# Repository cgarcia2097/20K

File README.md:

# numpad
Repository for the numpad project

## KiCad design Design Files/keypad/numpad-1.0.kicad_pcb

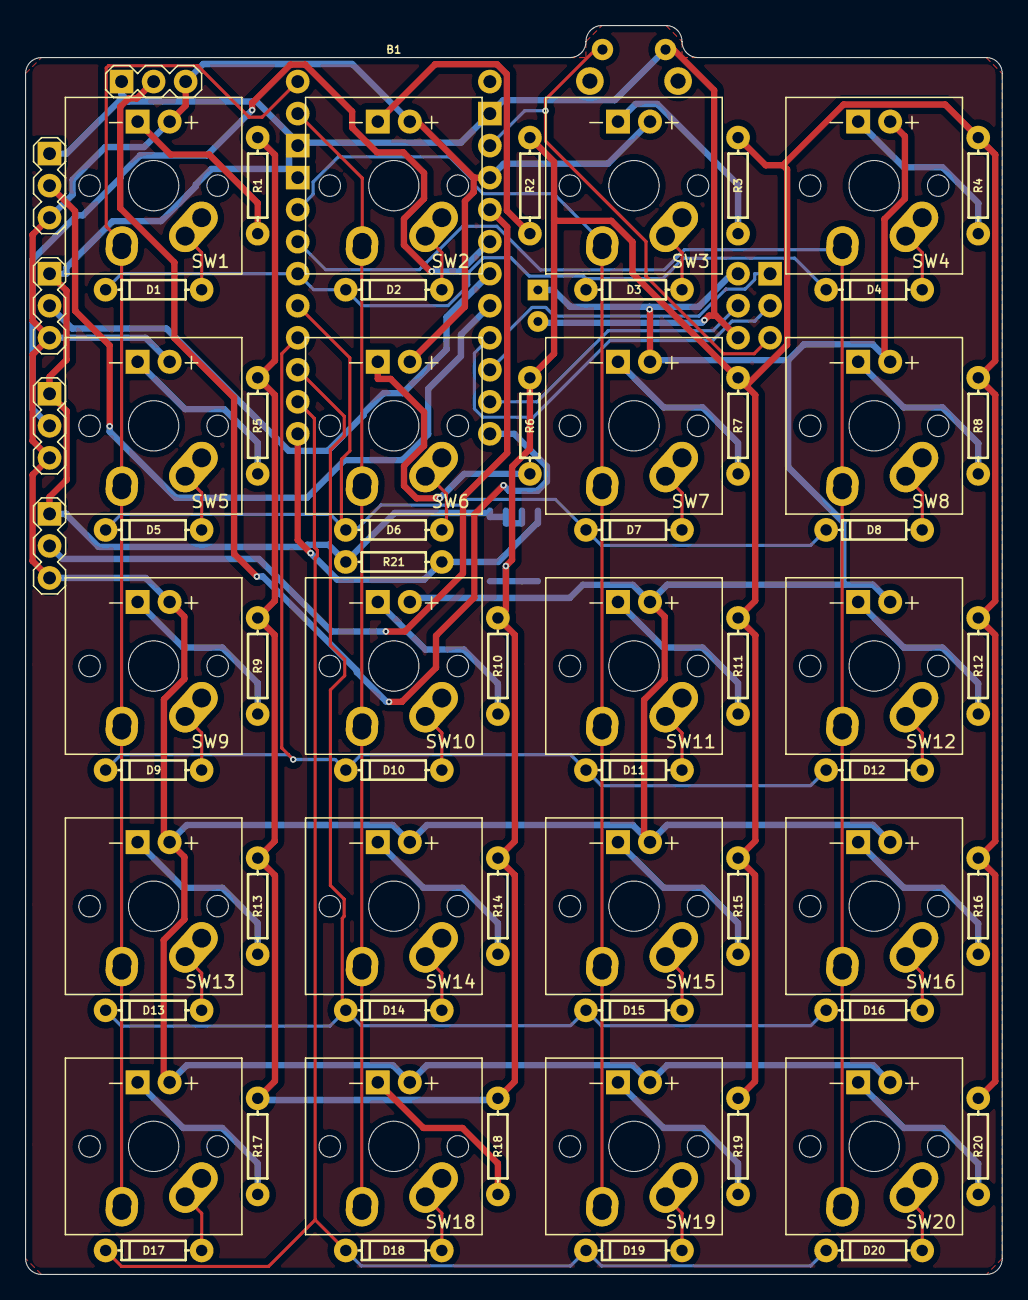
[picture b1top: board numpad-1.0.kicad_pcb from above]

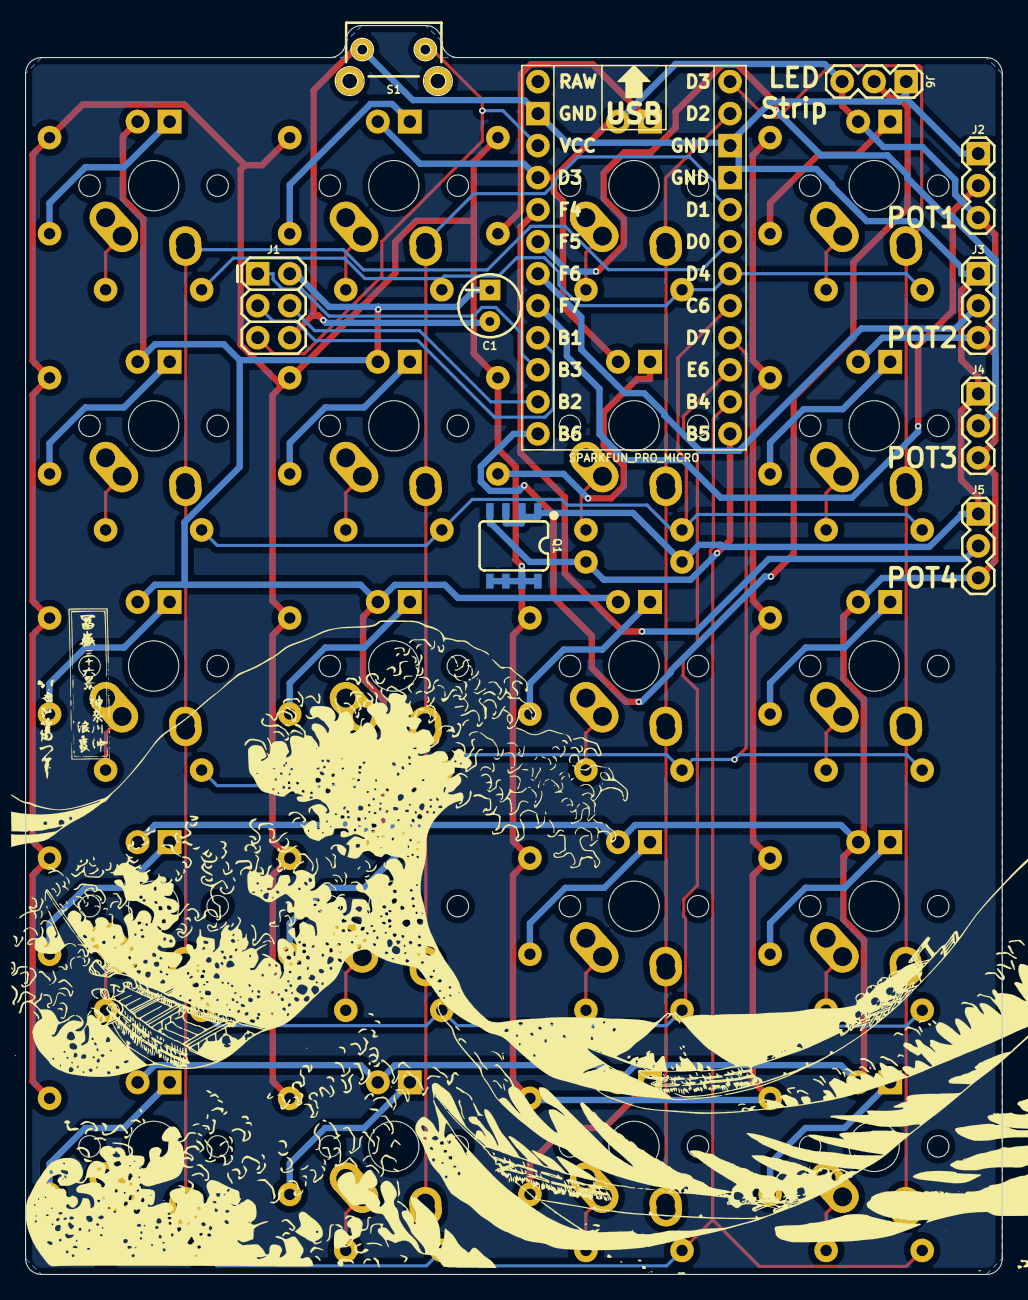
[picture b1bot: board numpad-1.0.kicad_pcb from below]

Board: 2 copper layers, 77.5 x 99.1 mm, 71 parts (9 on the bottom side), 62 nets.

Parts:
B1: SPARKFUN_PRO_MICRO
C1: 10UF-POLAR-RADIAL-2.5MM-25V-20%; CPOL-RADIAL-2.5MM-5MM
D1, D2, D3, D4, D5, D6, D7, D8, D9, D10, D11, D12, D13, D14, D15, D16, D17, D18, D19, D20: 1N4148; DIODE-1N4148
J1: Conn_02x03_Odd_Even; 2X3
J2, J3, J4, J5, J6: Conn_01x03; 1X03
Q1: MOSFET-NCH-FDS6630A; SO08
R1, R2, R3, R4, R5, R6, R7, R8, R9, R10, R11, R12, R13, R14, R15, R16, R17, R18, R19, R20, R21: RESISTORAXIAL-0.3; AXIAL-0.3
S1: MOMENTARY-SWITCH-SPST-PTH-RIGHT-ANGLE-KIT; TACTILE_SWITCH_PTH_RIGHT_ANGLE_KIT
SW1, SW2, SW3, SW4, SW5, SW6, SW7, SW8, SW9, SW10, SW11, SW12, SW13, SW14, SW15, SW16, SW17, SW18, SW19, SW20: KEYSW_LED; MX_ALPS_LED_PCB_MOUNT_1.0

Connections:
A0: B1.17, J2.2
A1: B1.18, J3.2
A2: B1.19, J4.2
A3: B1.20, J5.2
BACKLIGHT_CTRL: B1.12, Q1.4, R21.P$2
COL_1: B1.1, SW1.S2, SW5.S2, SW9.S2, SW13.S2, SW17.S2
COL_2: B1.2, SW2.S2, SW6.S2, SW10.S2, SW14.S2, SW18.S2
COL_3: B1.5, SW3.S2, SW7.S2, SW11.S2, SW15.S2, SW19.S2
COL_4: B1.6, SW4.S2, SW8.S2, SW12.S2, SW16.S2, SW20.S2
GND: B1.3, B1.4, B1.23, C1.2, J1.6, J2.3, J3.3, J4.3, J5.3, J6.3, Q1.1, Q1.2, Q1.3, R21.P$1, S1.2
LED_GND: Q1.5, Q1.6, Q1.7, Q1.8, R1.P$1, R2.P$1, R3.P$1, R4.P$1, R5.P$1, R6.P$1, R7.P$1, R8.P$1, R9.P$1, R10.P$1, R11.P$1, R12.P$1, R13.P$1, R14.P$1, R15.P$1, R16.P$1, R17.P$1, R18.P$1, R19.P$1, R20.P$1
MISO: B1.15, J1.1
MOSI: B1.14, J1.4
NEOPIXEL_CTRL: B1.13, J6.2
unnamed: D1.A, SW1.S1
unnamed: D2.A, SW2.S1
unnamed: D3.A, SW3.S1
unnamed: D4.A, SW4.S1
unnamed: D5.A, SW5.S1
unnamed: D6.A, SW6.S1
unnamed: D7.A, SW7.S1
unnamed: D8.A, SW8.S1
unnamed: D9.A, SW9.S1
unnamed: D10.A, SW10.S1
unnamed: D11.A, SW11.S1
unnamed: D12.A, SW12.S1
unnamed: D13.A, SW13.S1
unnamed: D14.A, SW14.S1
unnamed: D15.A, SW15.S1
unnamed: D16.A, SW16.S1
unnamed: D17.A, SW17.S1
unnamed: D18.A, SW18.S1
unnamed: D19.A, SW19.S1
unnamed: D20.A, SW20.S1
unnamed: R1.P$2, SW1.K
unnamed: R2.P$2, SW2.K
unnamed: R3.P$2, SW3.K
unnamed: R4.P$2, SW4.K
unnamed: R5.P$2, SW5.K
unnamed: R6.P$2, SW6.K
unnamed: R7.P$2, SW7.K
unnamed: R8.P$2, SW8.K
unnamed: R9.P$2, SW9.K
unnamed: R10.P$2, SW10.K
unnamed: R11.P$2, SW11.K
unnamed: R12.P$2, SW12.K
unnamed: R13.P$2, SW13.K
unnamed: R14.P$2, SW14.K
unnamed: R15.P$2, SW15.K
unnamed: R16.P$2, SW16.K
unnamed: R17.P$2, SW17.K
unnamed: R18.P$2, SW18.K
unnamed: R19.P$2, SW19.K
unnamed: R20.P$2, SW20.K
RESET: B1.22, J1.5, S1.1
ROW_1: B1.7, D1.C, D2.C, D3.C, D4.C
ROW_2: B1.8, D5.C, D6.C, D7.C, D8.C
ROW_3: B1.9, D9.C, D10.C, D11.C, D12.C
ROW_4: B1.10, D13.C, D14.C, D15.C, D16.C
ROW_5: B1.11, D17.C, D18.C, D19.C, D20.C
SCK: B1.16, J1.3
VCC: B1.21, C1.1, J1.2, J2.1, J3.1, J4.1, J5.1, J6.1, SW1.A, SW2.A, SW3.A, SW4.A, SW5.A, SW6.A, SW7.A, SW8.A, SW9.A, SW10.A, SW11.A, SW12.A, SW13.A, SW14.A, SW15.A, SW16.A, SW17.A, SW18.A, SW19.A, SW20.A

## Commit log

2019-11-27 Added case files
2020-04-13 Added kbdfirmware port
2020-07-25 Updated numpad cases
2020-07-26 Updated case files and updated project directories
2020-11-22 A lot of updates
